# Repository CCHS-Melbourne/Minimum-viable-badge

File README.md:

Minimum Viable Badge - Just the facts.
=============

This project is designed to be the absolute minimum number of components to do a badge.

[Schematic Design](Minimum-viable-schematic.pdf?raw=true "Schematic")

FEATURES
--------

* ESP32 based.
* CP2102 USB to serial.
* eInk Display.

CREDITS
------------

Made at hackmelbourne.org!

This project was designed by the 2018 linux.conf.au Open Hardware Team!
 - [Bob Powers](https://github.com/rdpowers)
 - [John Spencer](https://github.com/mage0r)
 - [Angus Gratton](https://github.com/projectgus)
 - [Andy Gelme](https://github.com/geekscape)
 - [Jon Oxer](https://github.com/jonoxer)
 - [Mark Wolfe](https://github.com/wolfeidau)

SPECIAL THANKS
------------

To the HackMelbourne (CCHS, http://hackmelbourne.org) community of Melbourne, Australia.

To all other open-source developers whose countless hours supported every other aspect of this design.

DISTRIBUTION
------------
The specific terms of distribution of this project are governed by the
license referenced below. Please contact the copyright owner if you wish to modify the board for distribution. Please utilize this design for personal or research projects. Please acknowledge all contributors.

LICENSE
-------
Licensed under the TAPR Open Hardware License (www.tapr.org/OHL).
The "license" sub-folder also contains a copy of this license in plain text format.

Copyright John Spencer, Bob Powers, Angus Gratton, Andy Gelme, Jon Oxer, Mark Wolfe 2017

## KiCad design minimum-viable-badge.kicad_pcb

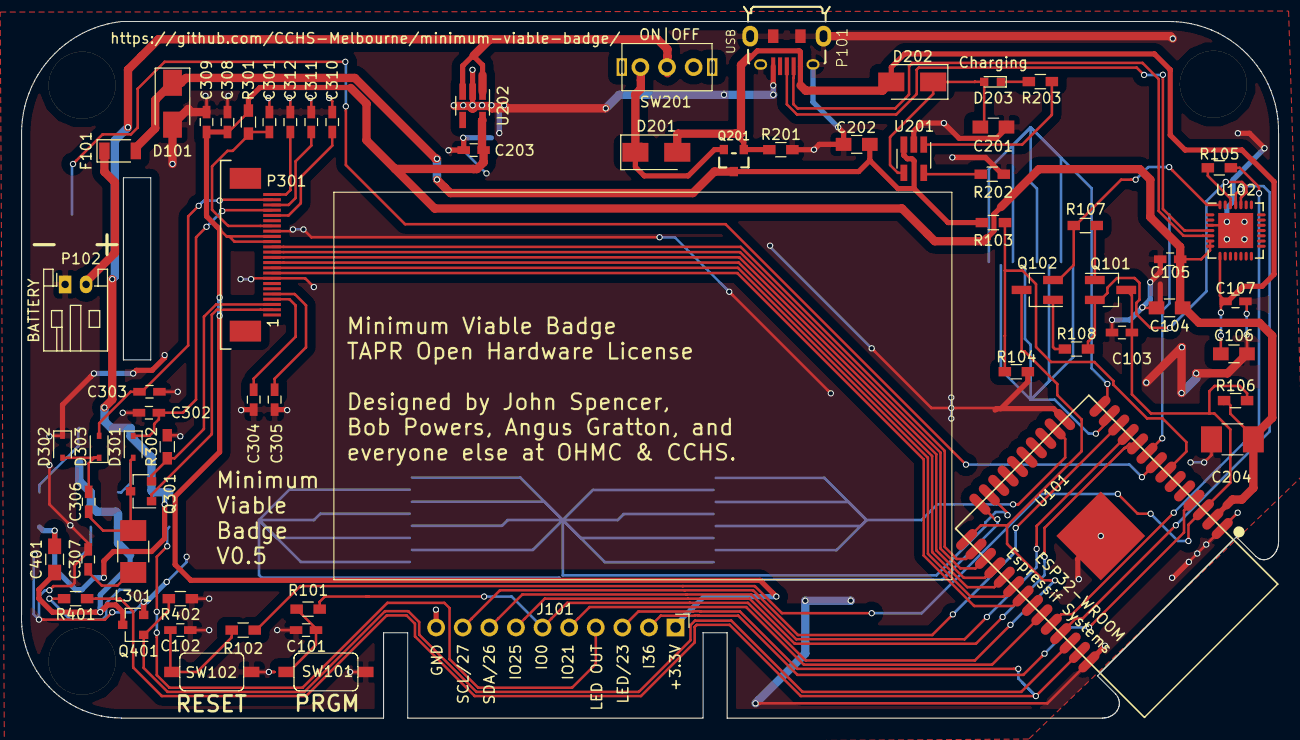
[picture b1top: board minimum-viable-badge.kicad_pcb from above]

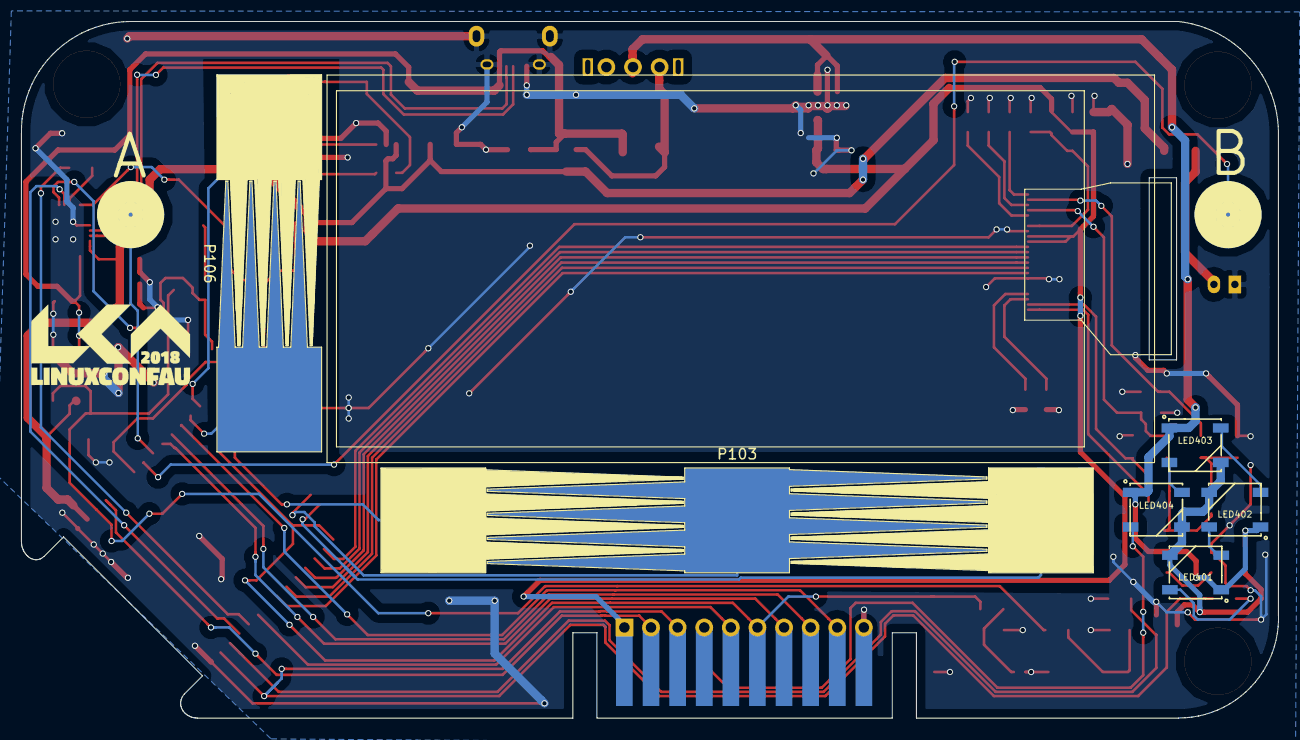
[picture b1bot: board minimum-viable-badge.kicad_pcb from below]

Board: 2 copper layers, 120.0 x 66.5 mm, 75 parts (8 on the bottom side), 64 nets.

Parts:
C101, C102: 1uF 6.3V; C_0603_HandSoldering
C103, C203, C301: 1uF; C_0603_HandSoldering
C104, C106: 10uF; C_0805_HandSoldering
C105, C107: 0.1uF; C_0603_HandSoldering
C201, C202, C401: 4.7uF; C_0805_HandSoldering
C204: 100uF 10V X5R; C_1210_HandSoldering
C302, C303, C304, C305, C306, C307, C308, C309, C310, C311, C312: 1uF 25V; C_0603_HandSoldering
D101, D201, D202: SS14; D_SMA
D203: CHRG; LED_0603
D301, D302, D303: SD103AWS; D_SOD-323
F101: 1A PTC; D_1206
J101: EDGE_CONNECTOR; Edge_Connector_S20-2.54-5_bottomsideonly
L301: 47uH 410MA; C_1210_HandSoldering
LED401, LED402, LED403, LED404: WS2812B
P101: USB; USB-MICRO-5pin_PTHMOUNT-Amphenol.10118194-0001LF
P102: BATTERY; JST_PH_S2B-PH-K_02x2.00mm_Angled
P103: POT_LONG; sense_long
P104: BUTTON_A; buttons
P105: BUTTON_B; buttons
P106: POT_SHORT; sense_short
P107, P108, P109: MECH; MountingHole_3.2mm_M3_Pad
P301: eInk; FPC_0.5mm_Pitch_24_Pin
Q101, Q102: S8050; SOT-23_Handsoldering
Q201: FDN340P; SOT23_FET
Q301: IRLML0030TRPBF; SOT-23
Q401: Q_NMOS_GSD; SOT-23
R101, R102, R105, R203, R401: 470R; R_0603_HandSoldering
R103: 1M 1%; R_0603_HandSoldering
R104: 100K 1%; R_0603_HandSoldering
R106, R201, R402: 12K; R_0603_HandSoldering
R107, R108: 12K(1%); R_0603_HandSoldering
R202: 2K 5%; R_0603_HandSoldering
R301: 0R; R_0603_HandSoldering
R302: 2R7, 1%; R_0603_HandSoldering
SW101: PRGM; K2-1107st
SW102: RESET; K2-1107st
SW201: ON|OFF; SK12D07VG3
U101: ESP32-WROOM
U102: CP2102; QFN-28-1EP_5x5mm_Pitch0.5mm
U201: MCP73831; SOT-23-5_HandSoldering
U202: XC6210A33MR-G; SOT-23-5_HandSoldering

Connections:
+3V3: C104.1, C105.1, C203.1, C204.1, C308.2, C309.2, J101.1, P301.15, P301.16, R106.2, R301.1, U101.2, U102.6, U102.7, U202.5
/BAT+: C202.1, D101.1, F101.2, Q201.2, R103.2, U201.3
/BAT_MON: R103.1, R104.1, U101.7
/DTR: Q102.2, R107.2, U102.28
/E-Ink Display/GDR: P301.2, Q301.1
/E-Ink Display/LCD_VDD: C301.2, P301.18, R301.2
/E-Ink Display/PREVGH: C302.1, D301.1, P301.21
/E-Ink Display/PREVGL: C303.1, D303.2, P301.23
/E-Ink Display/RESE: P301.3, Q301.2, R302.1
/E-Ink Display/VCOM: C312.1, P301.24
/E-Ink Display/VGH: C305.1, P301.5
/E-Ink Display/VGL: C304.1, P301.4
/E-Ink Display/VSH: C310.1, P301.20
/E-Ink Display/VSL: C311.1, P301.22
/EINK_BUSY: P301.9, U101.31
/EINK_CS: P301.12, U101.28
/EINK_D/C: P301.11, U101.29
/EINK_MOSI: P301.14, U101.26
/EINK_RST: P301.10, U101.30
/EINK_SCLK: P301.13, U101.27
/EN: C103.1, Q101.3, R102.1, R106.1, U101.3
/I2C_SCL: J101.9, U101.12
/I2C_SDA: J101.8, U101.11
/I36: J101.2, U101.4
/IO0: J101.6, Q102.3, R101.1, U101.25
/IO2: P103.1, U101.24
/IO12: P106.1, U101.14
/IO13: P103.3, U101.16
/IO14: P106.2, U101.13
/IO15: P103.2, U101.23
/IO21: J101.5, U101.33
/IO22: Q401.1, R402.1, U101.36
/IO23: J101.3, R401.2, U101.37
/IO25: J101.7, U101.10
/IO32: P105.1, U101.8
/IO33: P104.1, U101.9
/LED BlinkenLights/LED_GND: C401.2, LED401.3, LED402.3, LED403.3, LED404.3, Q401.3
/LED_DOUT: J101.4, LED404.2
/LED_VIN: C401.1, LED401.1, LED402.1, LED403.1, LED404.1, SW201.2, U202.1, U202.3
/RTS: Q101.2, R108.2, U102.24
/RXD: U101.35, U102.25
/TXD: R105.1, U101.34
/USB_D+: P101.3, U102.4
/USB_D-: P101.2, U102.5
/USB_VCC: C106.1, C107.1, D201.2, D202.2, P101.1, Q201.1, R201.1, U102.8
/hipster-power/UNREG_V: D201.1, Q201.3, SW201.1
GND: C101.2, C102.2, C103.2, C104.2, C105.2, C106.2, C107.2, C201.2, C202.2, C203.2, C204.2, C301.1, C302.2, C303.2, C304.2, C305.2, C307.2, C308.1, C309.1, C310.2, C311.2, C312.2, D101.2, D302.1, J101.10, P101.5, P101.6, P102.1, P301.8, P301.17, Q401.2, R104.2, R201.2, R202.2, R302.2, R402.2, SW101.1, SW102.1, U101.1, U101.15, U101.38, U101.39, U102.3, U102.29, U201.2, U202.2
unnamed: C101.1, R101.2, SW101.2
unnamed: C102.1, R102.2, SW102.2
unnamed: C201.1, D202.1, D203.2, U201.4
unnamed: C306.1, D301.2, L301.2, Q301.3
unnamed: C306.2, D302.2, D303.1
unnamed: C307.1, L301.1
unnamed: D203.1, R203.2
unnamed: F101.1, P102.2
unnamed: LED401.2, LED402.4
unnamed: LED401.4, R401.1
unnamed: LED402.2, LED403.4
unnamed: LED403.2, LED404.4
unnamed: Q101.1, R107.1
unnamed: Q102.1, R108.1
unnamed: R105.2, U102.26
unnamed: R202.1, U201.5
unnamed: R203.1, U201.1

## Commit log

2017-05-15 :octocat: Added .gitattributes & .gitignore files
2017-06-04 Initial commit
    Basic Schematic is already in place.
2017-06-04 Added readme and pdf schematic
2017-06-05 Now with less Hipster :(
2017-06-06 Updated cap sense.
2017-06-06 Minor changes to the pcb.
    Still testing ideas.
2017-06-07 More pcb work
2017-06-08 Updated pcb layout.
2017-06-13 Damnit. S8050 backwards
    Thanks https://github.com/rdpowers. Fixes #2
2017-06-13 Added some digikey links.
2017-07-10 Updated Schematic PDF
2017-08-25 updated touch sensors
2017-08-26 Added eInk decoupling caps.
2017-08-27 Updated Schematic
2017-08-28 Extra touch buttons
    and edge connector!
2017-08-28 Remove power LED
    Will reduce deep sleep power consumption to 1% or less of previous.
    Ref #6.
2017-08-28 power: Swap BJT for FET in power selection circuit
    Went with FDN340P as used on ESPlant, but any appropriately rated FET will do.
    Closes #12
2017-08-28 Add capacitor to EN pin
    Prevents problems with auto-reset
2017-08-28 Regenerate schematic PDF
2017-08-30 Arrange & label schematic, pass ERC
2017-08-30 Add e-ink gate drive circuitry
    Closes #14
2017-08-31 Added team to readme file.
2017-08-31 New outlines for the larger badge
2017-08-31 PCB new outline added
2017-08-31 Set component footprints.
2017-09-02 Placement started
    Predicting Bob will end up changing all this
2017-09-03 More footprint layout.
2017-09-03 Minor updates to schematic components.
2017-09-03 Picked inductor.
2017-09-03 Added pushbutton footprint
2017-09-03 Keeping everything in sync.
2017-09-03 Updated footprint for buttons.
2017-09-03 New Switch Library
2017-09-03 Updated with toggle marked on Eco2.usr
2017-09-03 Updated to use new switch.
2017-09-03 Changed drive circuitry Schottky diodes to SOD323.
2017-09-03 many more components added to the pcb
2017-09-03 LCD pins routed to ESP32
2017-09-03 broken lcd routes
2017-09-03 hrm, these pins are kind of funky
2017-09-03 Shuffling around our touch sensor pins.
2017-09-03 Hey, that looks like a board!
2017-09-03 Minor updates.
2017-09-03 Flipped is better.
2017-09-03 Swap battery connector to JST PH 2.0
2017-09-03 Ground planes, power nets, move bulk cap close to ESP32
2017-09-03 Add missing stitching vias on other side of eink data lines
2017-09-06 Swap C307 0603->0805
2017-09-06 Add SZLCSC part links
2017-09-06 Rename power switch SK12D07VG5 -> SK12D07VG3
2017-09-07 Added edge connector and button silkscreen
2017-09-11 Schematic parts libraries: Consolidate in one minimum-viable-badge-parts.lib
2017-09-11 Change 3.3V reg to XC6210, enlarge board to move power switch
2017-09-11 Fixed some connections. added vias
2017-09-11 Fixed edge layer.
2017-09-11 Added Linux.conf.au Logo
2017-09-11 Moved buttons around.
    This might work!
2017-09-13 Fix power switch label
    Closes #19
2017-09-13 Fix battery label polarity on silkscreen
    Closes #18
2017-09-19 Correct e-ink connector direction, reposition & reroute board
    Closes #20
2017-09-19 Place ground plane over the horizontal touch slider
2017-09-19 Move switchmode parts out from under battery. Partially routed...
2017-09-19 Some updating of pinmap before branch, need updating again.
2017-09-19 Making some progress on moving the battery connector & boost converter.
2017-09-19 Some prospective positions & routing. Needs a bit of work, but looking much better.
2017-09-19 I don't know what wasn't saved, but it wasn't major.
2017-09-19 Finish routing changes, add some labels
2017-09-19 Move credits to under battery
2017-09-19 Silkscreen cleanup
2017-09-20 Moved eInk bus off of opposite of back slider.
2017-09-24 Add WS2812Bs for Blinkenlights
2017-09-24 Route LEDs, make edge connector one sided with mounting slots
2017-09-24 Swap to use DEPG0290BNS75AF0-compatible components
2017-09-24 Fix J101 label
2017-09-24 Fix some orphaned stitching vias
2017-09-24 More stitching via cleanup
2017-09-24 Add more ground plane around the LEDs
2017-09-25 Cosmetic tidy up
